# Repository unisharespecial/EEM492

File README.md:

# EEM492---B-T-RME-PROJES--II
 EEM492 - BİTİRME PROJESİ II

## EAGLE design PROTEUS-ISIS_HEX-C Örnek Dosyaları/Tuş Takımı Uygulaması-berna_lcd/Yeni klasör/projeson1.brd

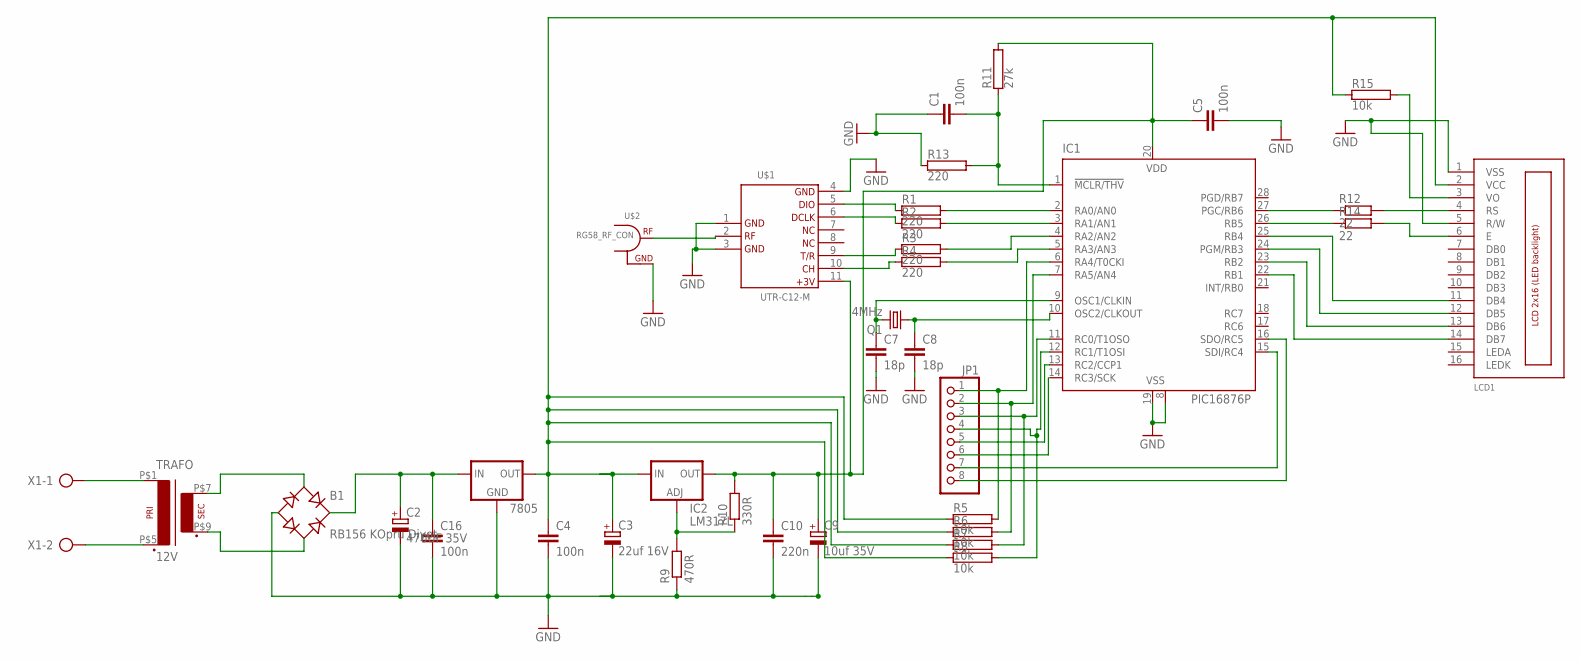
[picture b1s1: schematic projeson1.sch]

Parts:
7805: 78XXS
B1: RB156 KOpru Diyot; RB1A
C1: 100n; C025-030X050
C2: 470UF 35V; E3,5-10
C3: 22uf 16V; E2,5-7
C4, C16: 100n; C050-025X075
C5: 100n; C025-025X050
C7, C8: 18p; C025-025X050
C9: 10uf 35V; E2,5-7
C10: 220n; C050-025X075
IC1: PIC16876P; DIL28-3
IC2: LM317L; 317L
JP1: PINHD-1X8; 1X08
LCD1: LCD_2X16_SIL; HY-1602F
Q1: 4MHz; HC49/S
R1, R2, R3, R4, R13: 220; AC04
R5, R6, R7, R8, R15: 10k; AC04
R9: 470R; 0207/10
R10: 330R; 0207/10
R11: 27k; AC04
R12, R14: 22; 0204/5
TRAFO: 12V; E3031TRF
U$1: UTR-C12-M
U$2: RG58_RF_CON
X1: AK300/3

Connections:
GND: 7805.GND, B1.-, C1.1, C2.-, C3.-, C4.2, C5.2, C7.2, C8.2, C9.-, C10.2, C16.2, IC1.8 (VSS), IC1.19 (VSS), LCD1.1 (VSS), LCD1.5 (R/W), R9.1, R13.1, U$1.1, U$1.3, U$1.4, U$2.GND
unnamed: R1.1, U$1.5
unnamed: R3.1, U$1.9
unnamed: IC1.4 (RA2/AN2), R3.2
unnamed: R4.1, U$1.10
unnamed: IC1.2 (RA0/AN0), R1.2
unnamed: IC1.3 (RA1/AN1), R2.2
unnamed: LCD1.6 (E), R14.2
unnamed: IC1.5 (RA3/AN3), R4.2
unnamed: LCD1.3 (VO), R15.2
unnamed: IC1.6 (RA4/T0CKI), JP1.1, R5.2
unnamed: IC1.7 (RA5/AN4), JP1.2, R6.2
unnamed: IC1.11 (RC0/T1OSO), JP1.3, R7.2
unnamed: IC1.12 (RC1/T1OSI), JP1.4, R8.2
unnamed: IC1.13 (RC2/CCP1), JP1.5
unnamed: IC1.15 (SDI/RC4), JP1.7
unnamed: IC1.16 (SDO/RC5), JP1.8
unnamed: LCD1.4 (RS), R12.2
unnamed: IC1.26 (RB5), R14.1
unnamed: IC1.25 (RB4), LCD1.11 (DB4)
unnamed: IC1.24 (PGM/RB3), LCD1.12 (DB5)
unnamed: IC1.23 (RB2), LCD1.13 (DB6)
unnamed: IC1.22 (RB1), LCD1.14 (DB7)
unnamed: TRAFO.P$5 (5), X1.2
unnamed: B1.AC1, TRAFO.P$7 (7)
unnamed: B1.AC2, TRAFO.P$9 (9)
unnamed: 7805.IN, B1.+, C2.+, C16.1
unnamed: TRAFO.P$1 (1), X1.1
unnamed: IC2.1 (ADJ), R9.2, R10.1
unnamed: IC1.27 (PGC/RB6), R12.1
unnamed: U$1.2, U$2.RF
unnamed: C1.2, IC1.1 (!MCLR/THV), R11.1, R13.2
unnamed: C7.1, IC1.9 (OSC1/CLKIN), Q1.2
unnamed: C8.1, IC1.10 (OSC2/CLKOUT), Q1.1
unnamed: R2.1, U$1.6
unnamed: 7805.OUT, C3.+, C4.1, IC2.3 (IN), LCD1.2 (VCC), R5.1, R6.1, R7.1, R8.1, R15.1
unnamed: C5.1, C9.+, C10.1, IC1.20 (VDD), IC2.2 (OUT), R10.2, R11.2, U$1.11

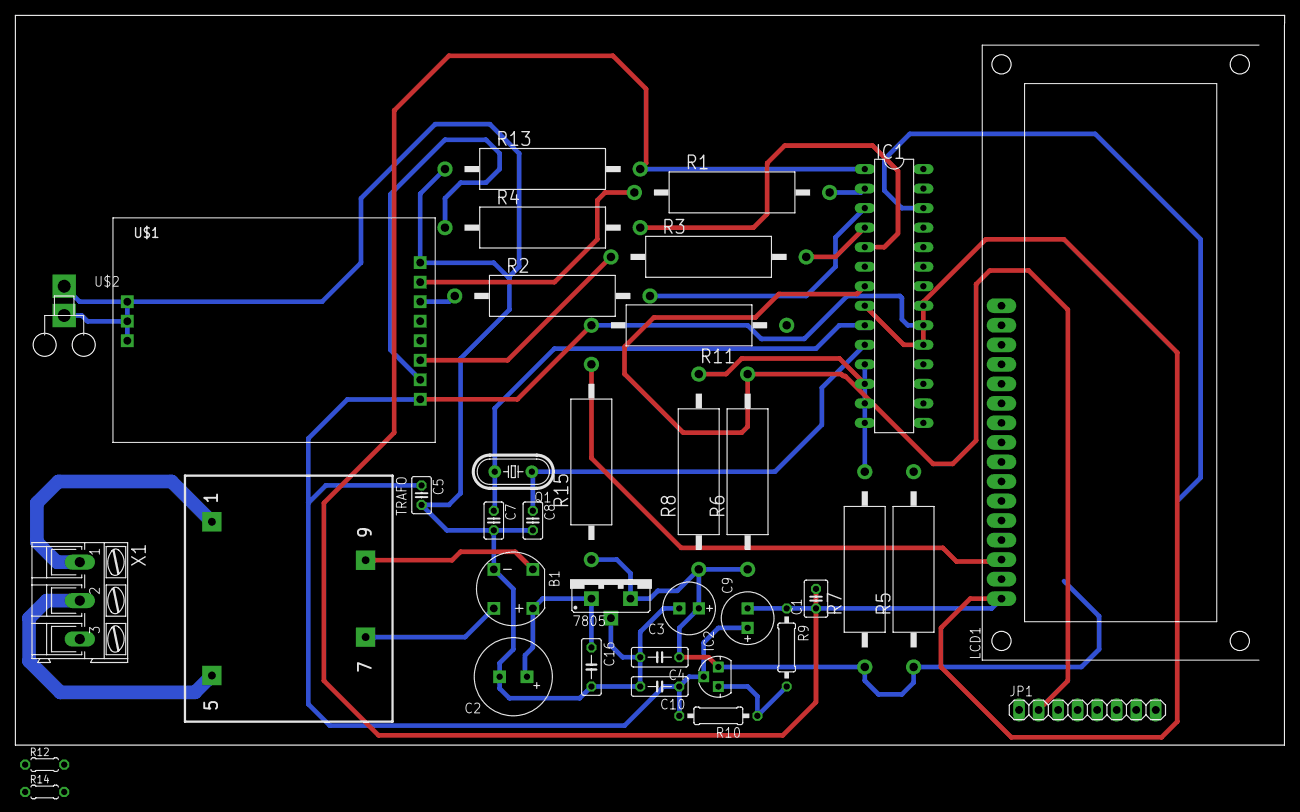
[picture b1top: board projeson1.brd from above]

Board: 2 copper layers, 165.1 x 94.9 mm, 36 parts (0 on the bottom side), 37 nets.

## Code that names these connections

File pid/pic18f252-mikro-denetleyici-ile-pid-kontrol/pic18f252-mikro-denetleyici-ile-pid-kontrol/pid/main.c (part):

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#define MIN_SPEED 1
#define MAX_STEP 1

#define RIGHT_DIRECTION RA4
#define LEFT_DIRECTION RB5

/*Right = A = Bottom*/
#define RIGHT_PWM_H CCPR1L
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#define BACKWARD_LEFT 0
#define FORWARD_RIGHT 0
#define BACKWARD_RIGHT 1
#define RIGHT_BRAKE RA2
#define LEFT_BRAKE RA3

#define DEBUG 0
#define DEBUG_ALL 0 
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    char c;

    TRISA = 0xFE; 
	//RA0 = 1;
    Initialize();
    PwmInitialize();

    serial_init();
	//RA0 = 1;

    while(1)
    { 	
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            }
            else if(c == 'b')
            {
                RA2 ^= 1;
				RA3 ^= 1;
                printf("Brakes: %d, %d", RA2, RA3);
            }
			else if(c == 'p')
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    CCP2CON = 0b00000101;
    IPEN = 1;           
    INTEDG0 = 0;        // RB0 interrupt on falling edge
    INTEDG1 = 1;        // RB1 interrupt on rising edge
    INTEDG2 = 1;        // RB2 interrupt on rising edge
    INT1IP = 1;         // Set RB1 to be high priority interrupt
    INT2IP = 1;         // Set RB2 to be high priority interrupt
	INT0IE = 1;         // Enable interrupts on RB0
    INT1IE = 1;         // Enabled interrupts on RB1
    INT2IE = 1;         // Enabled interrupts on RB2
    CCP2IP = 1;         // Setup HiPri
    RA2 = 1;            // Release Right Brake
    RA3 = 1;            // Release Left Brake
    GIE = 1;            // 
    GIEH = 1;           // Setup HiPri,
    GIEL = 1;
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
    if(SSPIF == 1)
    {
		RA0 = 1;
        if(msg_index == 0)
		{
			if( current_tx_message == NULL )
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		{
			SSPBUF = current_tx_message[msg_index];
		}
		RA0 = 0;
    }

	if(TMR1IF == 1)
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{
#if 0
    static unsigned char alive_count = 250;
    RA0 = 1;
    if(--alive_count == 0)
    {
        alive_count = 250;
        RA0 = 0;
    }
#endif
}
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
